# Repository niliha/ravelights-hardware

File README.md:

# ravelights-hardware

This repository contains various PCB designs for driving WS28XX LED strips and other light fixtures.

The READMEs in the subdirectories provide more details.

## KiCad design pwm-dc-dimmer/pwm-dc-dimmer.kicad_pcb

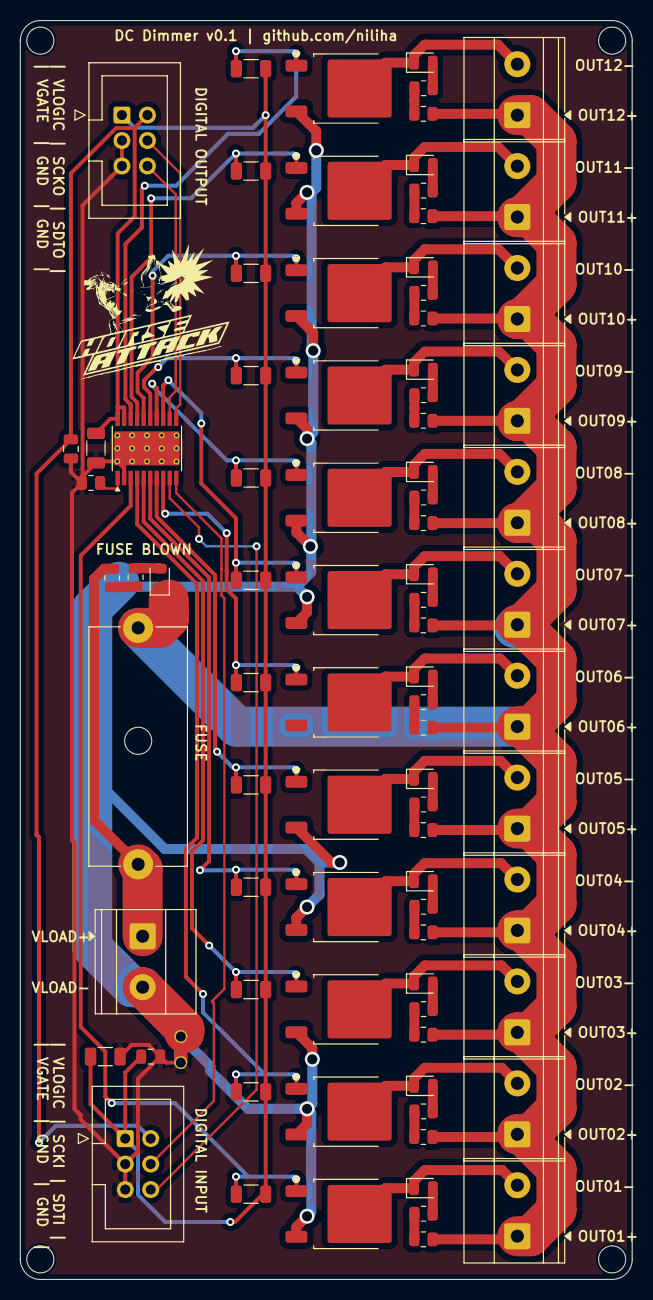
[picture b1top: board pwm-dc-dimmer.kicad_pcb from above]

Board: 2 copper layers, 61.0 x 125.5 mm, 90 parts (0 on the bottom side), 61 nets.

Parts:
C1, C3: 100nF; C_0805_2012Metric
C2, C4: 10uF; C_1206_3216Metric
D1, D2, D3, D4, D5, D6, D7, D8, D9, D10, D11, D12, D13: LED; LED_0805_2012Metric
F1: Fuse; fuseholder
H1, H2, H3, H4: MountingHole; MountingHole_2.7mm_M2.5_ISO7380
J1, J2, J3, J4, J5, J6, J7, J8, J9, J10, J11, J12, J13: Screw_Terminal_01x02; TerminalBlock_Phoenix_MKDS-1,5-2-5.08_1x02_P5.08mm_Horizont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
J14, J15: Conn_02x03_Odd_Even; IDC-Header_2x03_P2.54mm_Vertical
NT1: NetTie_2; NetTie-2_THT_Pad1.0mm
Q1, Q2, Q3, Q4, Q5, Q6, Q7, Q8, Q9, Q10, Q11, Q12: Q_NMOS_GDS; TO-252-2
R1: 3K; R_0805_2012Metric
R2, R3, R4, R5, R6, R7, R8, R9, R10, R11, R12, R13: 300R; R_1206_3216Metric
R14, R15, R16, R17, R18, R19, R20, R21, R22, R23, R24, R25, R26, R27, R28, R29, R30, R31, R32, R33, R34, R35, R36, R37, R38, R39: 10K; R_0805_2012Metric
U1: HTSSOP-20-1EP_4.4x6.5mm_P0.65mm_EP3.4x6.5mm_ThermalVias

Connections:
/Channel 1/LED_LOAD_BETWEEN_RESISTORS: R14.2, R26.1
/Channel 1/LED_LOAD_CATHODE: D1.2 (A), R26.2
/Channel 2/LED_LOAD_BETWEEN_RESISTORS: R15.2, R27.1
/Channel 2/LED_LOAD_CATHODE: D2.2 (A), R27.2
/Channel 3/LED_LOAD_BETWEEN_RESISTORS: R16.2, R28.1
/Channel 3/LED_LOAD_CATHODE: D3.2 (A), R28.2
/Channel 4/LED_LOAD_BETWEEN_RESISTORS: R17.2, R29.1
/Channel 4/LED_LOAD_CATHODE: D4.2 (A), R29.2
/Channel 5/LED_LOAD_BETWEEN_RESISTORS: R18.2, R30.1
/Channel 5/LED_LOAD_CATHODE: D5.2 (A), R30.2
/Channel 6/LED_LOAD_BETWEEN_RESISTORS: R19.2, R31.1
/Channel 6/LED_LOAD_CATHODE: D6.2 (A), R31.2
/Channel 7/LED_LOAD_BETWEEN_RESISTORS: R20.2, R32.1
/Channel 7/LED_LOAD_CATHODE: D7.2 (A), R32.2
/Channel 8/LED_LOAD_BETWEEN_RESISTORS: R21.2, R33.1
/Channel 8/LED_LOAD_CATHODE: D8.2 (A), R33.2
/Channel 9/LED_LOAD_BETWEEN_RESISTORS: R22.2, R34.1
/Channel 9/LED_LOAD_CATHODE: D9.2 (A), R34.2
/Channel 10/LED_LOAD_BETWEEN_RESISTORS: R23.2, R35.1
/Channel 10/LED_LOAD_CATHODE: D10.2 (A), R35.2
/Channel 11/LED_LOAD_BETWEEN_RESISTORS: R24.2, R36.1
/Channel 11/LED_LOAD_CATHODE: D11.2 (A), R36.2
/Channel 12/LED_LOAD_BETWEEN_RESISTORS: R25.2, R37.1
/Channel 12/LED_LOAD_CATHODE: D12.2 (A), R37.2
/FUSE_LED_CATHODE: D13.2 (A), R39.2
/FUSE_LED_RESISTORS: R38.2, R39.1
GATE_SINK_1: Q1.1 (G), R3.2, U1.3 (OUT0)
GATE_SINK_2: Q2.1 (G), R2.2, U1.4 (OUT1)
GATE_SINK_3: Q3.1 (G), R4.2, U1.5 (OUT2)
GATE_SINK_4: Q4.1 (G), R5.2, U1.6 (OUT3)
GATE_SINK_5: Q5.1 (G), R6.2, U1.7 (OUT4)
GATE_SINK_6: Q6.1 (G), R7.2, U1.8 (OUT5)
GATE_SINK_7: Q7.1 (G), R8.2, U1.13 (OUT6)
GATE_SINK_8: Q8.1 (G), R9.2, U1.14 (OUT7)
GATE_SINK_9: Q9.1 (G), R10.2, U1.15 (OUT8)
GATE_SINK_10: Q10.1 (G), R11.2, U1.16 (OUT9)
GATE_SINK_11: Q11.1 (G), R12.2, U1.17 (OUT10)
GATE_SINK_12: Q12.1 (G), R13.2, U1.18 (OUT11)
GND: C1.2, C2.2, C3.2, C4.2, J14.3, J14.5, J15.3, J15.5, NT1.2, R1.2, U1.2 (GND), U1.21 (EP)
GND_LOAD: J13.2, NT1.1, Q1.3 (S), Q2.3 (S), Q3.3 (S), Q4.3 (S), Q5.3 (S), Q6.3 (S), Q7.3 (S), Q8.3 (S), Q9.3 (S), Q10.3 (S), Q11.3 (S), Q12.3 (S)
unnamed: R1.1, U1.1 (IREF)
OUT1-: D1.1 (K), J1.2, Q1.2 (D)
OUT2-: D2.1 (K), J2.2, Q2.2 (D)
OUT3-: D3.1 (K), J3.2, Q3.2 (D)
OUT4-: D4.1 (K), J4.2, Q4.2 (D)
OUT5-: D5.1 (K), J5.2, Q5.2 (D)
OUT6-: D6.1 (K), J6.2, Q6.2 (D)
OUT7-: D7.1 (K), J7.2, Q7.2 (D)
OUT8-: D8.1 (K), J8.2, Q8.2 (D)
OUT9-: D9.1 (K), J9.2, Q9.2 (D)
OUT10-: D10.1 (K), J10.2, Q10.2 (D)
OUT11-: D11.1 (K), J11.2, Q11.2 (D)
OUT12-: D12.1 (K), J12.2, Q12.2 (D)
SCKI: J15.4, U1.10 (SCKI)
SCKO: J14.4, U1.11 (SCKO)
SDTI: J15.6, U1.9 (SDTI)
SDTO: J14.6, U1.12 (SDTO)
V_GATE: C3.1, C4.1, J14.1, J15.1, R2.1, R3.1, R4.1, R5.1, R6.1, R7.1, R8.1, R9.1, R10.1, R11.1, R12.1, R13.1
V_LOAD: F1.1, J13.1, R38.1
V_LOAD_FUSED: D13.1 (K), F1.2, J1.1, J2.1, J3.1, J4.1, J5.1, J6.1, J7.1, J8.1, J9.1, J10.1, J11.1, J12.1, R14.1, R15.1, R16.1, R17.1, R18.1, R19.1, R20.1, R21.1, R22.1, R23.1, R24.1, R25.1
V_LOGIC: C1.1, C2.1, J14.2, J15.2, U1.19 (VCC), U1.20 (VREG)

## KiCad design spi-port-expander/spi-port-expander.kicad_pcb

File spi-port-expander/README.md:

# SPI Port Expander

This is a breakout board for the [MCP23S17](https://www.microchip.com/en-us/product/MCP23S17) 16 channel SPI port expander.
Using hardware addressing mode, 8 of these port expanders can be driven on a single SPI bus with the same chip select line.

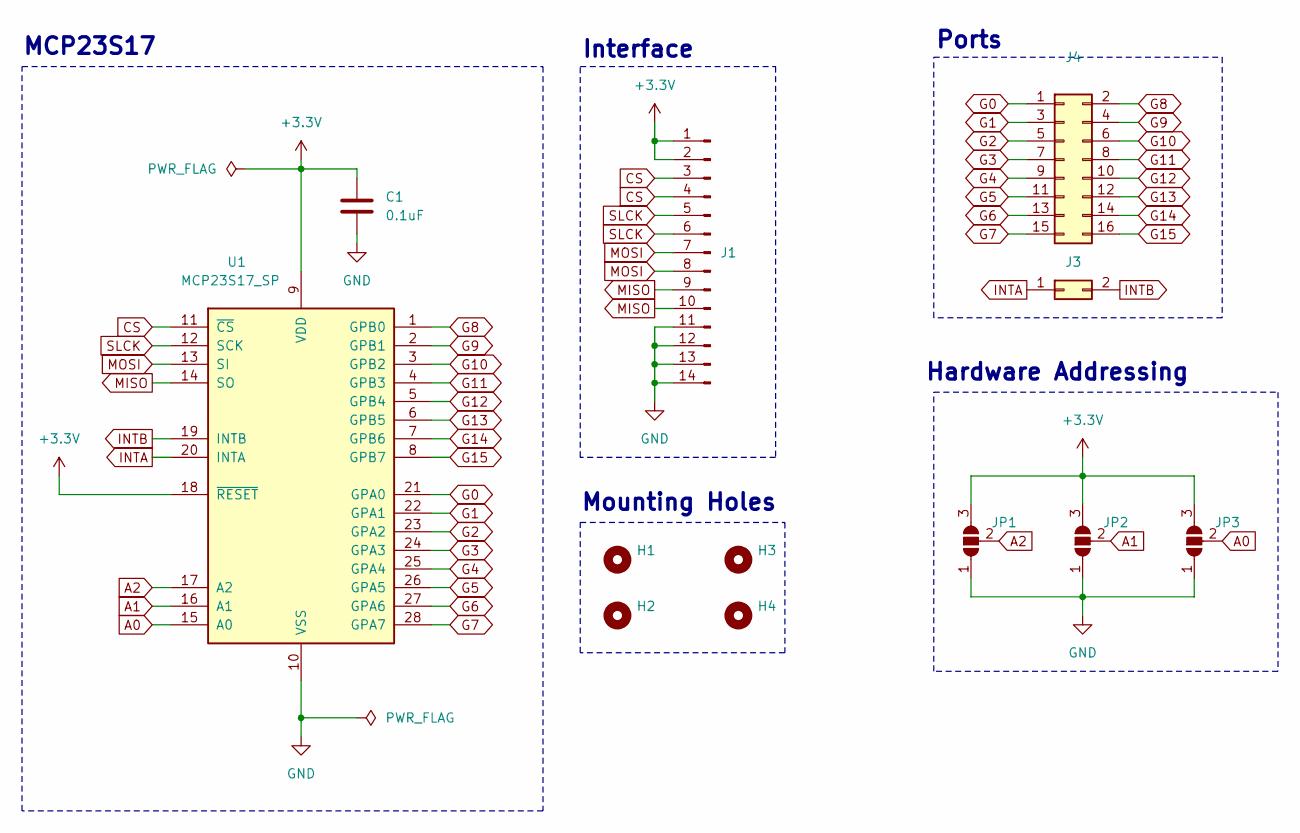
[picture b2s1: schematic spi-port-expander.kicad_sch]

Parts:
C1: 0.1uF; C_Disc_D5.0mm_W2.5mm_P5.00mm
H1, H2, H3, H4: MountingHole; MountingHole_2.7mm_M2.5
J1: Conn_01x14_Pin; PinHeader_1x14_P2.54mm_Vertical
J3: Conn_02x01; PinHeader_2x01_P2.54mm_Vertical
J4: Conn_02x08_Odd_Even; PinHeader_2x08_P2.54mm_Vertical
JP1, JP2, JP3: SolderJumper_3_Open; SolderJumper-3_P1.3mm_Open_Pad1.0x1.5mm
U1: MCP23S17_SP; DIP-28_W7.62mm

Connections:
+3.3V: C1.1, J1.1, J1.2, JP1.3 (B), JP2.3 (B), JP3.3 (B), U1.9 (VDD), U1.18 (~RESET)
A0: JP3.2 (C), U1.15 (A0)
A1: JP2.2 (C), U1.16 (A1)
A2: JP1.2 (C), U1.17 (A2)
CS: J1.3, J1.4, U1.11 (~CS)
G0: J4.1, U1.21 (GPA0)
G1: J4.3, U1.22 (GPA1)
G2: J4.5, U1.23 (GPA2)
G3: J4.7, U1.24 (GPA3)
G4: J4.9, U1.25 (GPA4)
G5: J4.11, U1.26 (GPA5)
G6: J4.13, U1.27 (GPA6)
G7: J4.15, U1.28 (GPA7)
G8: J4.2, U1.1 (GPB0)
G9: J4.4, U1.2 (GPB1)
G10: J4.6, U1.3 (GPB2)
G11: J4.8, U1.4 (GPB3)
G12: J4.10, U1.5 (GPB4)
G13: J4.12, U1.6 (GPB5)
G14: J4.14, U1.7 (GPB6)
G15: J4.16, U1.8 (GPB7)
GND: C1.2, J1.11, J1.12, J1.13, J1.14, JP1.1 (A), JP2.1 (A), JP3.1 (A), U1.10 (VSS)
INTA: J3.1, U1.20 (INTA)
INTB: J3.2, U1.19 (INTB)
MISO: J1.9, J1.10, U1.14 (SO)
MOSI: J1.7, J1.8, U1.13 (SI)
SLCK: J1.5, J1.6, U1.12 (SCK)

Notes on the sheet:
Ports
MCP23S17
Interface
Hardware Addressing
Mounting Holes

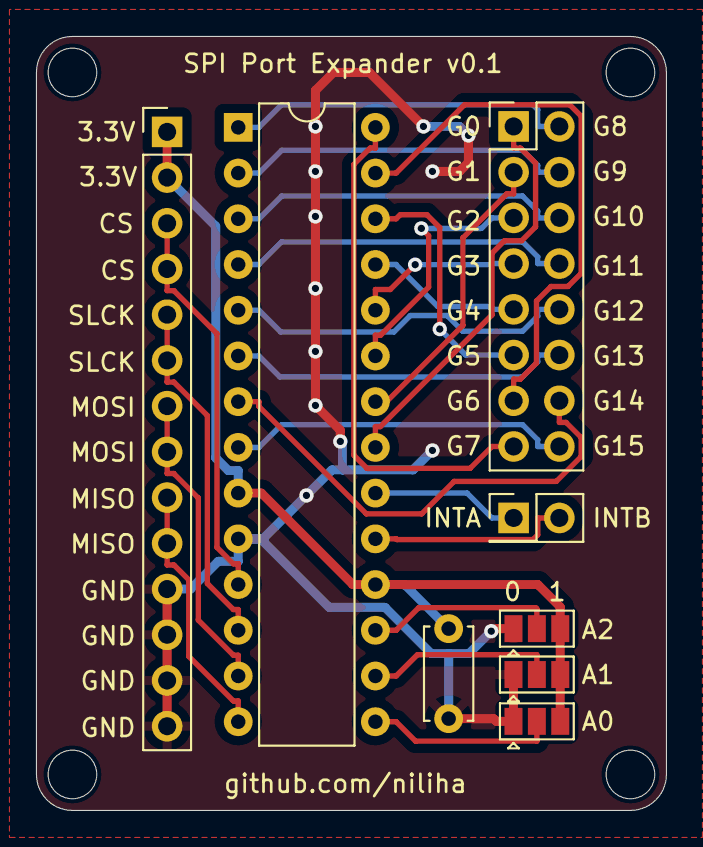
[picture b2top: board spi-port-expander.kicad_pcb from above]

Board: 2 copper layers, 35.0 x 43.0 mm, 12 parts (0 on the bottom side), 27 nets.

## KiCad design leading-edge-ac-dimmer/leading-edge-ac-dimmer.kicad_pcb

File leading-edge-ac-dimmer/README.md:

# Leading Edge 230V AC Dimmer

This PCB design allows to dim 8 incandescent light bulbs using a microcontroller.

**Note:** In version v0.1 there is a design error which leads to arcing on the snubber resistor.
This can be fixed by omitting the snubber circuit at the cost of not being able to drive inductive loads.
In a future revision, the snubber resistor will be replaced with a more suitable one.

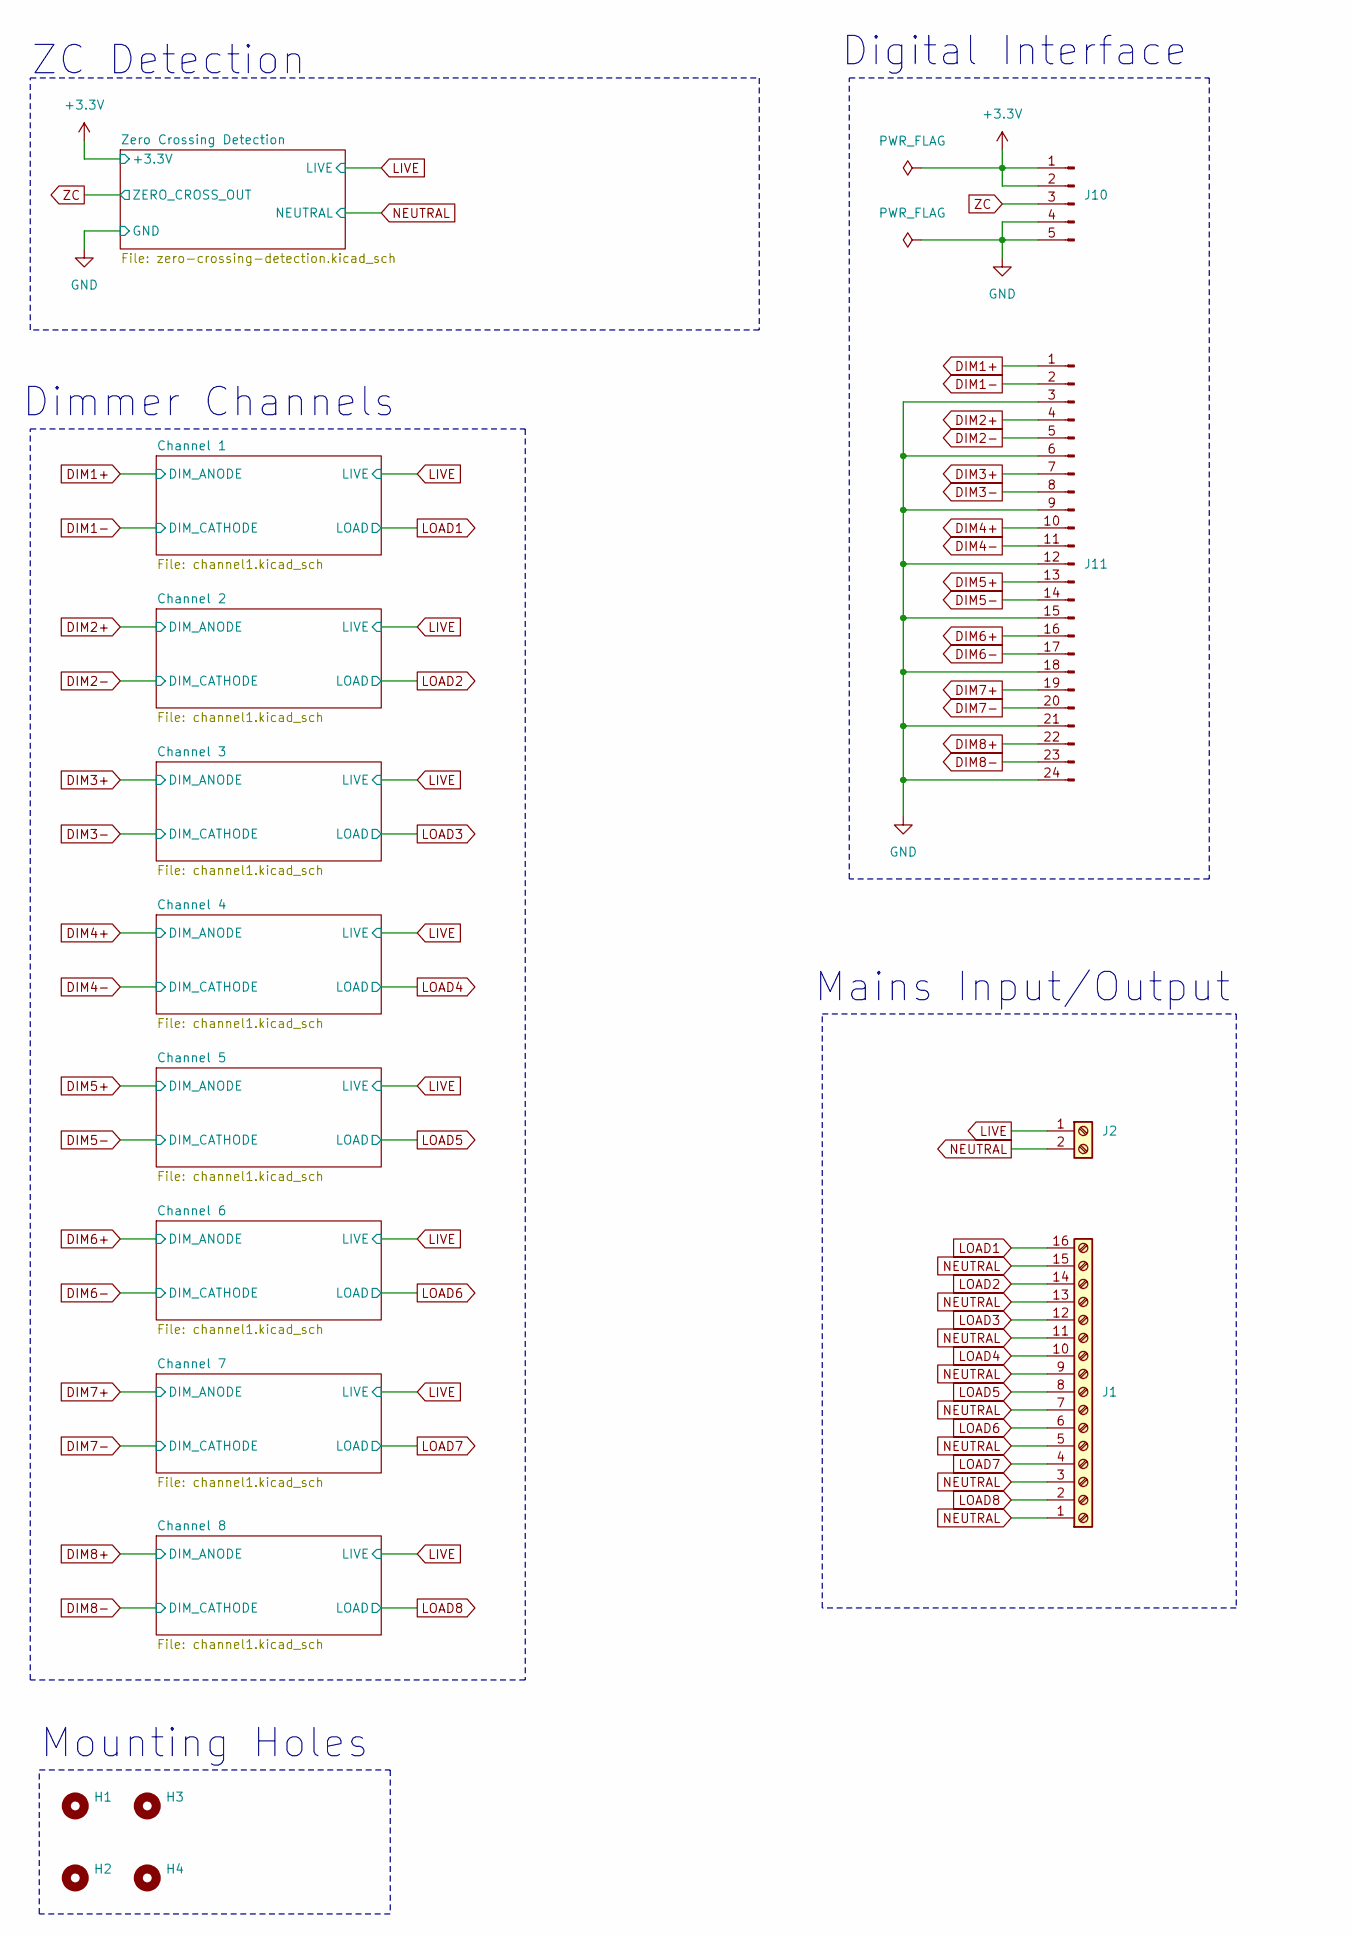
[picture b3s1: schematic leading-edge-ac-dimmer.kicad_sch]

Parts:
H1, H2, H3, H4: MountingHole; MountingHole_2.7mm_M2.5_ISO7380
J1: Screw_Terminal_01x16; TerminalBlock_Phoenix_MKDS-1,5-16-5.08_1x16_P5.08mm_Horizon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
J2: Screw_Terminal_01x02; TerminalBlock_Phoenix_MKDS-1,5-2-5.08_1x02_P5.08mm_Horizont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
J10: Conn_01x05_Pin; PinHeader_1x05_P2.54mm_Vertical
J11: Conn_01x24_Pin; PinHeader_1x24_P2.54mm_Vertical

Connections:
+3.3V: J10.1, J10.2; also elsewhere on the board
DIM1+: J11.1; also elsewhere on the board
DIM1-: J11.2; also elsewhere on the board
DIM2+: J11.4; also elsewhere on the board
DIM2-: J11.5; also elsewhere on the board
DIM3+: J11.7; also elsewhere on the board
DIM3-: J11.8; also elsewhere on the board
DIM4+: J11.10; also elsewhere on the board
DIM4-: J11.11; also elsewhere on the board
DIM5+: J11.13; also elsewhere on the board
DIM5-: J11.14; also elsewhere on the board
DIM6+: J11.16; also elsewhere on the board
DIM6-: J11.17; also elsewhere on the board
DIM7+: J11.19; also elsewhere on the board
DIM7-: J11.20; also elsewhere on the board
DIM8+: J11.22; also elsewhere on the board
DIM8-: J11.23; also elsewhere on the board
GND: J10.4, J10.5, J11.3, J11.6, J11.9, J11.12, J11.15, J11.18, J11.21, J11.24; also elsewhere on the board
LIVE: J2.1; also elsewhere on the board
LOAD1: J1.16; also elsewhere on the board
LOAD2: J1.14; also elsewhere on the board
LOAD3: J1.12; also elsewhere on the board
LOAD4: J1.10; also elsewhere on the board
LOAD5: J1.8; also elsewhere on the board
LOAD6: J1.6; also elsewhere on the board
LOAD7: J1.4; also elsewhere on the board
LOAD8: J1.2; also elsewhere on the board
NEUTRAL: J1.1, J1.3, J1.5, J1.7, J1.9, J1.11, J1.13, J1.15, J2.2; also elsewhere on the board
ZC: J10.3; also elsewhere on the board

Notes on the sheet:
Digital Interface
Mounting Holes
Dimmer Channels
Mains Input/Output
ZC Detection

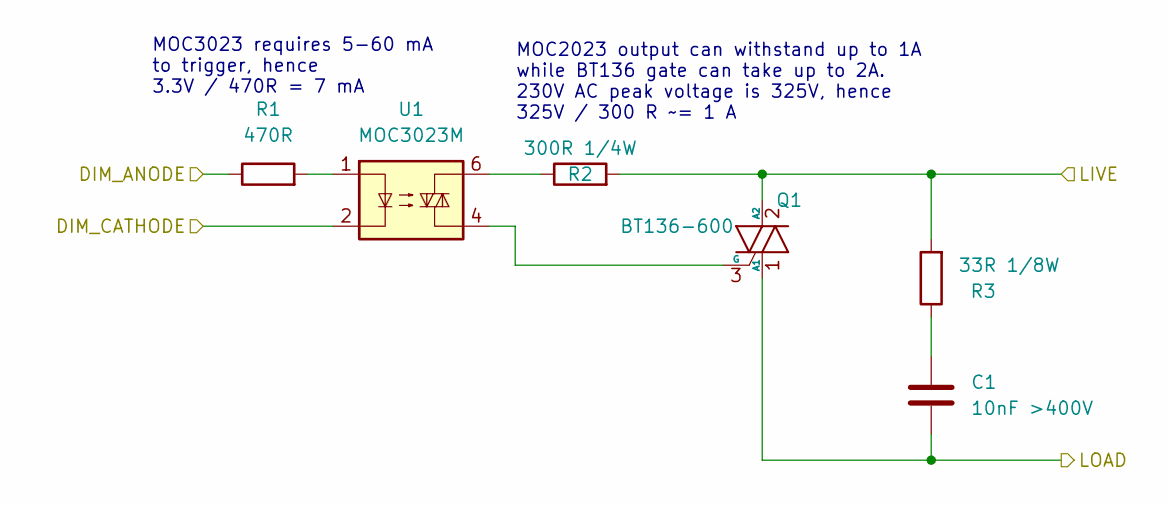
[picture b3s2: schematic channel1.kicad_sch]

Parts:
C1: 10nF >400V; C_1206_3216Metric
Q1: BT136-600; TO-252-2
R1: 470R; R_0805_2012Metric
R2: 300R 1/4W; R_1206_3216Metric
R3: 33R 1/8W; R_0805_2012Metric
U1: MOC3023M; Lite-On_SOP6_6.5x7.3mm_P2.54mm

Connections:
DIM1+: R1.1; also elsewhere on the board
DIM1-: U1.2; also elsewhere on the board
LIVE: Q1.2 (A2), R2.2, R3.2; also elsewhere on the board
LOAD1: C1.2, Q1.1 (A1); also elsewhere on the board
unnamed: C1.1, R3.1
unnamed: Q1.3 (G), U1.4
unnamed: R1.2, U1.1
unnamed: R2.1, U1.6

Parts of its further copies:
C2, C3, C4, C5, C6, C7, C8: 10nF >400V; C_1206_3216Metric
Q2, Q3, Q4, Q5, Q6, Q7, Q8: BT136-600; TO-252-2
R4, R7, R10, R13, R16, R19, R22: 470R; R_0805_2012Metric
R5, R8, R11, R14, R17, R20, R23: 300R 1/4W; R_1206_3216Metric
R6, R9, R12, R15, R18, R21, R24: 33R 1/8W; R_0805_2012Metric
U2, U3, U4, U5, U6, U7, U8: MOC3023M; Lite-On_SOP6_6.5x7.3mm_P2.54mm

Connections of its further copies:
DIM2+: R4.1; also elsewhere on the board
DIM2-: U2.2; also elsewhere on the board
DIM3+: R7.1; also elsewhere on the board
DIM3-: U3.2; also elsewhere on the board
DIM4+: R10.1; also elsewhere on the board
DIM4-: U4.2; also elsewhere on the board
DIM5+: R13.1; also elsewhere on the board
DIM5-: U5.2; also elsewhere on the board
DIM6+: R16.1; also elsewhere on the board
DIM6-: U6.2; also elsewhere on the board
DIM7+: R19.1; also elsewhere on the board
DIM7-: U7.2; also elsewhere on the board
DIM8+: R22.1; also elsewhere on the board
DIM8-: U8.2; also elsewhere on the board
LIVE: Q2.2 (A2), Q3.2 (A2), Q4.2 (A2), Q5.2 (A2), Q6.2 (A2), Q7.2 (A2), Q8.2 (A2), R5.2, R6.2, R8.2, R9.2, R11.2, R12.2, R14.2, R15.2, R17.2, R18.2, R20.2, R21.2, R23.2, R24.2; also elsewhere on the board
LOAD2: C2.2, Q2.1 (A1); also elsewhere on the board
LOAD3: C3.2, Q3.1 (A1); also elsewhere on the board
LOAD4: C4.2, Q4.1 (A1); also elsewhere on the board
LOAD5: C5.2, Q5.1 (A1); also elsewhere on the board
LOAD6: C6.2, Q6.1 (A1); also elsewhere on the board
LOAD7: C7.2, Q7.1 (A1); also elsewhere on the board
LOAD8: C8.2, Q8.1 (A1); also elsewhere on the board
unnamed: C2.1, R6.1
unnamed: C3.1, R9.1
unnamed: C4.1, R12.1
unnamed: C5.1, R15.1
unnamed: C6.1, R18.1
unnamed: C7.1, R21.1
unnamed: C8.1, R24.1
unnamed: Q2.3 (G), U2.4
unnamed: Q3.3 (G), U3.4
unnamed: Q4.3 (G), U4.4
unnamed: Q5.3 (G), U5.4
unnamed: Q6.3 (G), U6.4
unnamed: Q7.3 (G), U7.4
unnamed: Q8.3 (G), U8.4
unnamed: R4.2, U2.1
unnamed: R5.1, U2.6
unnamed: R7.2, U3.1
unnamed: R8.1, U3.6
unnamed: R10.2, U4.1
unnamed: R11.1, U4.6
unnamed: R13.2, U5.1
unnamed: R14.1, U5.6
unnamed: R16.2, U6.1
unnamed: R17.1, U6.6
unnamed: R19.2, U7.1
unnamed: R20.1, U7.6
unnamed: R22.2, U8.1
unnamed: R23.1, U8.6

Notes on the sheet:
MOC2023 output can withstand up to 1A while BT136 gate can take up to 2A. 230V AC peak voltage is 325V, hence 325V / 300 R ~= 1 A
MOC3023 requires 5-60 mA to trigger, hence 3.3V / 470R = 7 mA

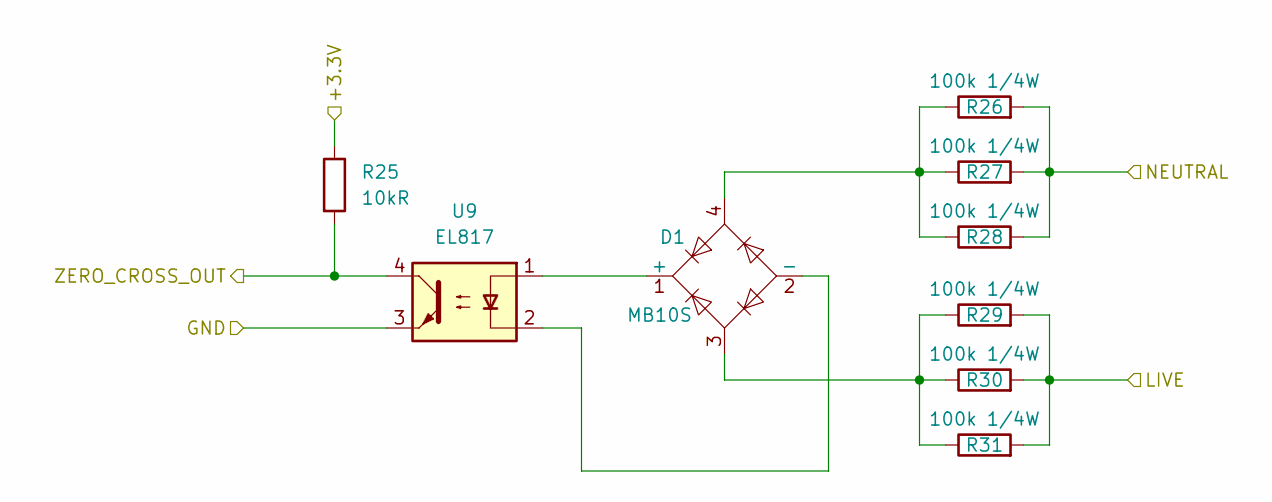
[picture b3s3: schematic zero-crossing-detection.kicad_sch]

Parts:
D1: MB10S; TO-269AA
R25: 10kR; R_0805_2012Metric
R26, R27, R28, R29, R30, R31: 100k 1/4W; R_1206_3216Metric
U9: EL817; SMDIP-4_W9.53mm

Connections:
+3.3V: R25.1; also elsewhere on the board
GND: U9.3; also elsewhere on the board
LIVE: R29.2, R30.2, R31.2; also elsewhere on the board
NEUTRAL: R26.2, R27.2, R28.2; also elsewhere on the board
unnamed: D1.1 (+), U9.1
unnamed: D1.2 (-), U9.2
unnamed: D1.3, R29.1, R30.1, R31.1
unnamed: D1.4, R26.1, R27.1, R28.1
ZC: R25.2, U9.4; also elsewhere on the board

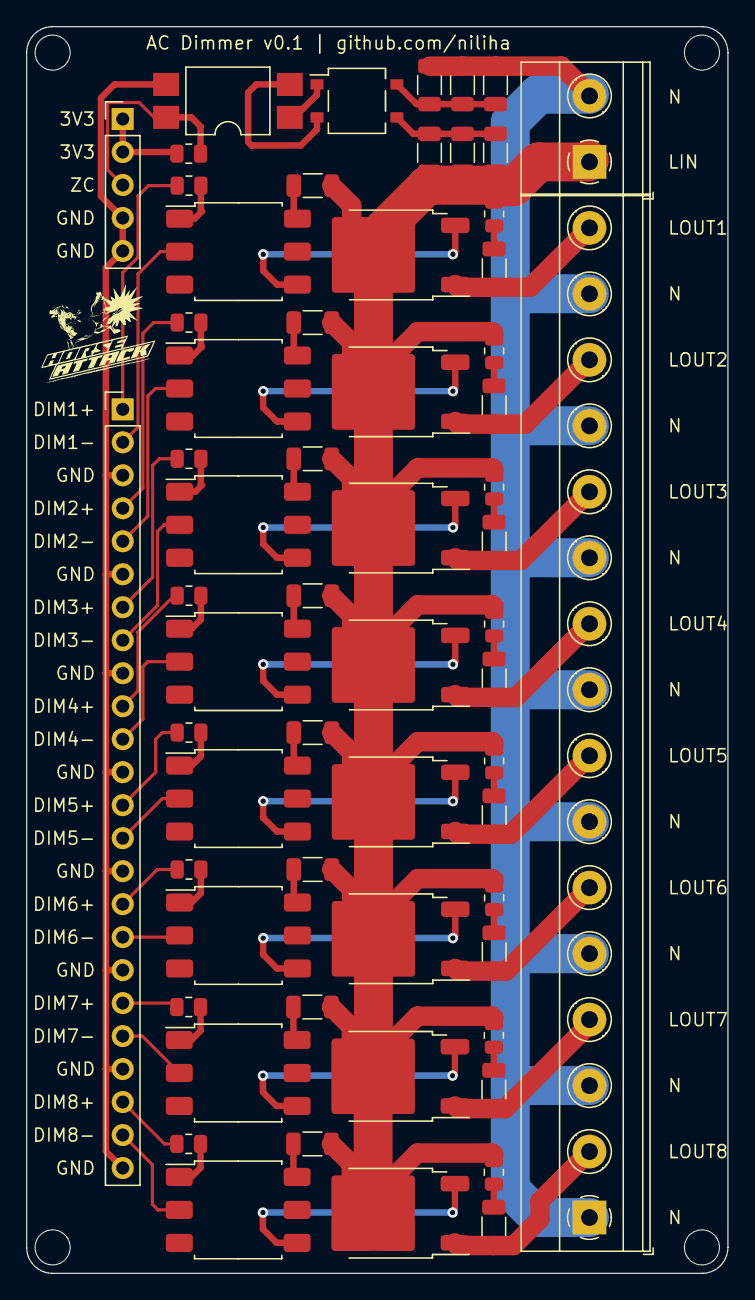
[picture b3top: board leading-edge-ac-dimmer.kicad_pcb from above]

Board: 2 copper layers, 54.0 x 96.0 mm, 65 parts (0 on the bottom side), 65 nets.

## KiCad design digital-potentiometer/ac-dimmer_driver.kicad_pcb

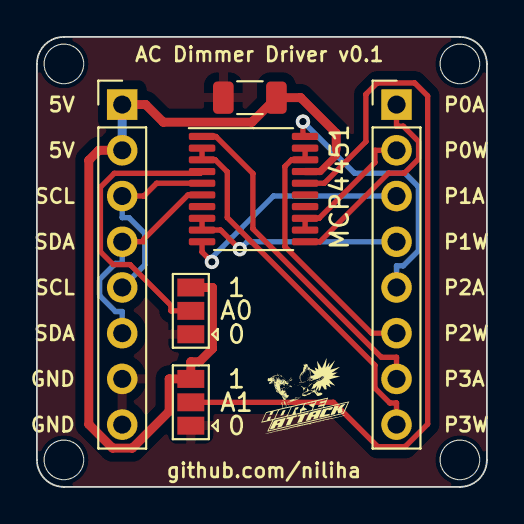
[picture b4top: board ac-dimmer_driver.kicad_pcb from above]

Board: 2 copper layers, 25.0 x 25.0 mm, 10 parts (0 on the bottom side), 14 nets.

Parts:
C1: 0.1uF; C_1206_3216Metric
H1, H2, H3, H4: MountingHole; MountingHole_2.2mm_M2
J1, J2: Conn_01x08_Pin; PinHeader_1x08_P2.54mm_Vertical
JP1, JP2: SolderJumper_3_Open; SolderJumper-3_P1.3mm_Open_Pad1.0x1.5mm
U1: MCP4451; TSSOP-20_4.4x6.5mm_P0.65mm

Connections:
+5V: C1.1, J2.1, J2.2, JP1.3 (B), JP2.3 (B), U1.17 (VDD)
/A0: JP1.2 (C), U1.4 (HVC/A0)
/A1: JP2.2 (C), U1.16 (A1)
GND: C1.2, J2.7, J2.8, JP1.1 (A), JP2.1 (A), U1.7 (VSS)
P0A: J1.1, U1.11 (P0A)
P0W: J1.2, U1.12 (P0W), U1.13 (P0B)
P1A: J1.3, U1.10 (P1A)
P1W: J1.4, U1.8 (P1B), U1.9 (P1W)
P2A: J1.5, U1.20 (P2A)
P2W: J1.6, U1.18 (P2B), U1.19 (P2W)
P3A: J1.7, U1.1 (P3A)
P3W: J1.8, U1.2 (P3W), U1.3 (P3B)
SCL_MCU: J2.3, J2.5, U1.5 (SCL)
SDA_MCU: J2.4, J2.6, U1.6 (SDA)

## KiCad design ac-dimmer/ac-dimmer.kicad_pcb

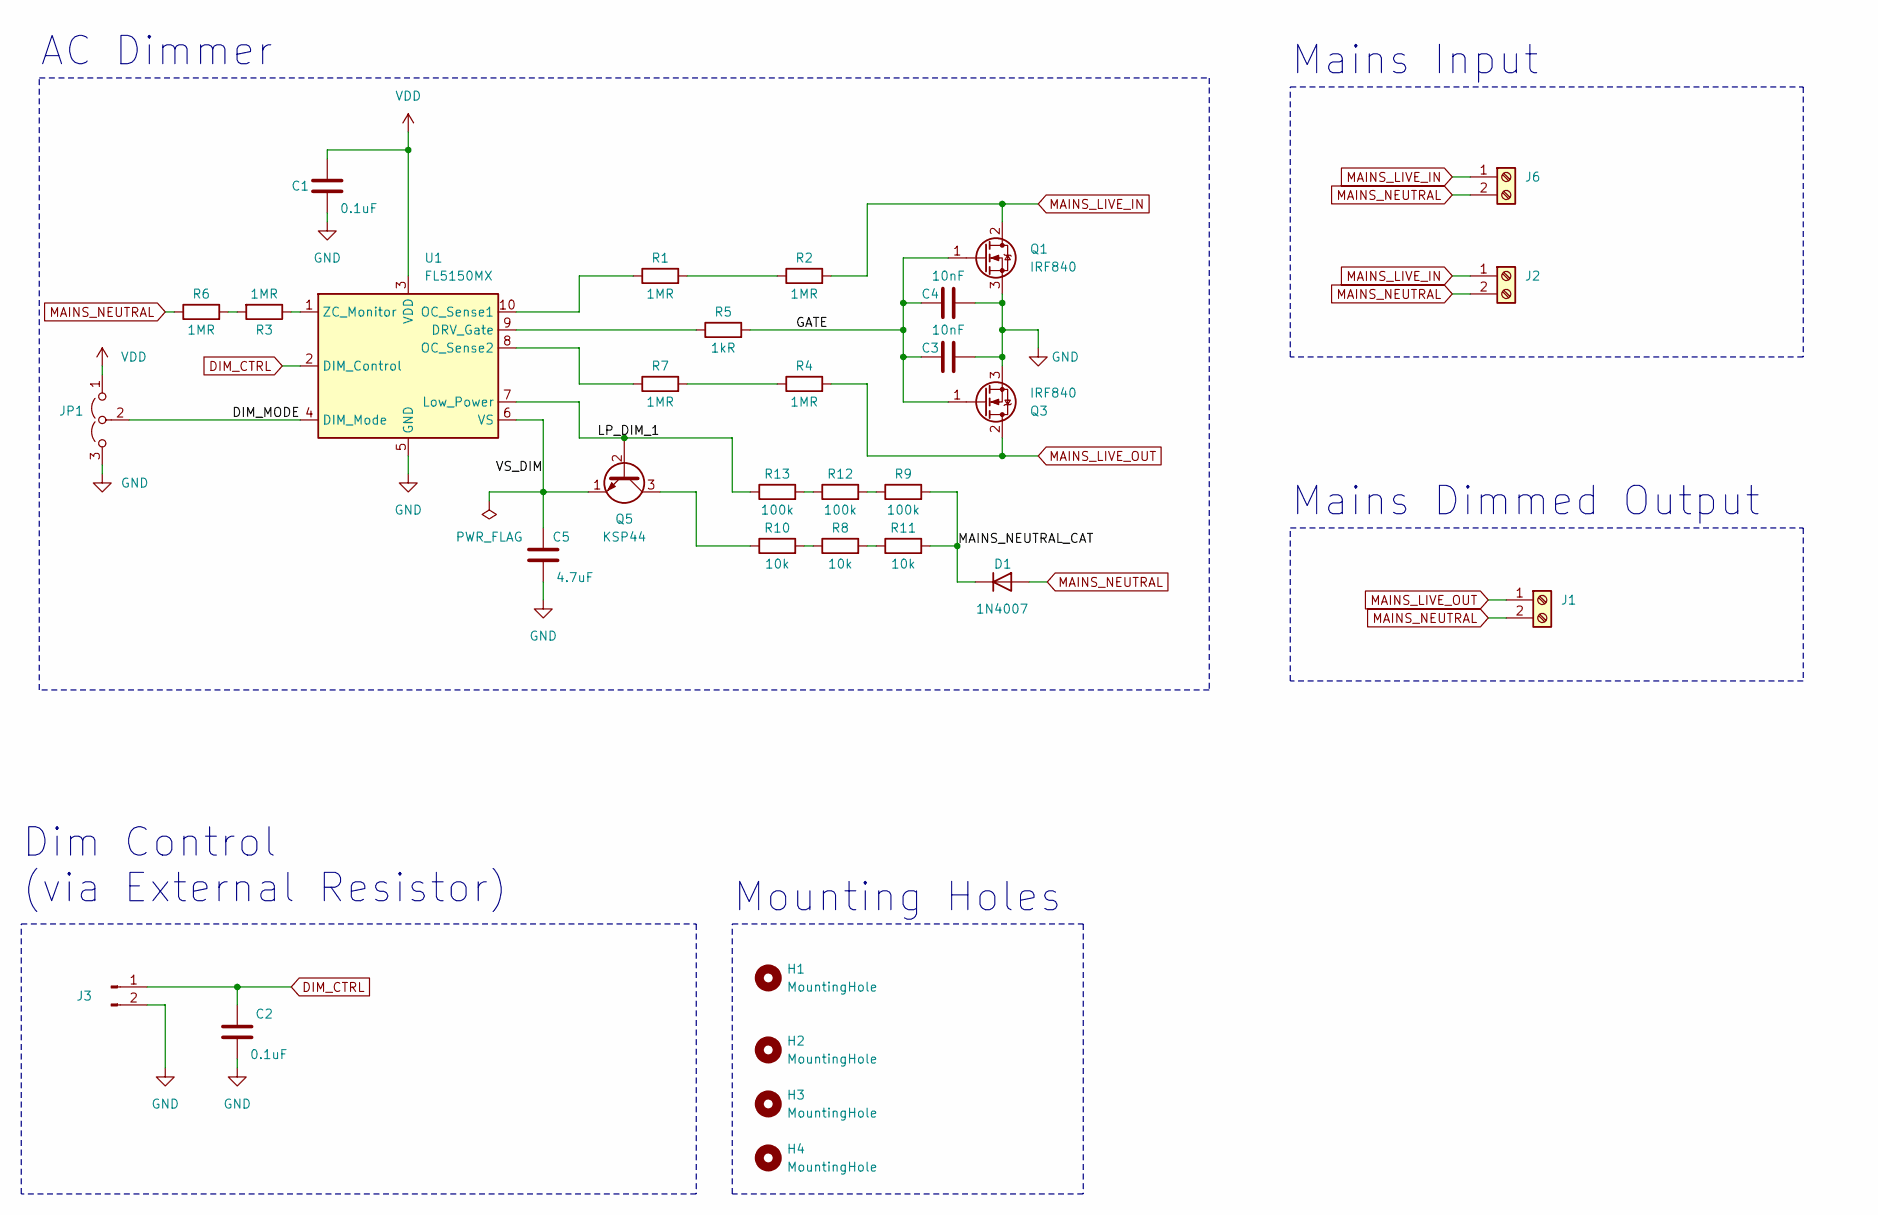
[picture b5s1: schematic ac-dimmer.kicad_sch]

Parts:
C1, C2: 0.1uF; C_1206_3216Metric
C3, C4: 10nF; C_1206_3216Metric
C5: 4.7uF; C_1206_3216Metric
D1: 1N4007; D_DO-41_SOD81_P10.16mm_Horizontal
H1, H2, H3, H4: MountingHole; MountingHole_2.7mm_M2.5_ISO7380
J1, J2, J6: Screw_Terminal_01x02; TerminalBlock_Phoenix_MKDS-1,5-2-5.08_1x02_P5.08mm_Horizont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
J3: Conn_01x02_Pin; PinHeader_1x02_P2.54mm_Vertical
JP1: Jumper_3_Open; PinHeader_1x03_P2.54mm_Vertical
Q1, Q3: IRF840; TO-220-3_Vertical
Q5: KSP44; TO-92_Inline
R1, R2, R3, R4, R6, R7: 1MR; R_1206_3216Metric
R5: 1kR; R_1206_3216Metric
R8, R10, R11: 10k; R_1206_3216Metric
R9, R12, R13: 100k; R_1206_3216Metric
U1: FL5150MX; SSOP-10_3.9x4.9mm_P1.00mm

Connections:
/DIM_MODE: JP1.2 (C), U1.4 (DIM_Mode)
/GATE: C3.1, C4.1, Q1.1 (G), Q3.1 (G), R5.2
/LP_DIM_1: Q5.2 (B), R13.1, U1.7 (Low_Power)
/MAINS_NEUTRAL_CAT: D1.1 (K), R9.2, R11.2
/VS_DIM: C5.1, Q5.1 (E), U1.6 (VS)
DIM_CTRL: C2.1, J3.1, U1.2 (DIM_Control)
GND: C1.2, C2.2, C3.2, C4.2, C5.2, J3.2, JP1.3 (B), Q1.3 (S), Q3.3 (S), U1.5 (GND)
MAINS_LIVE_IN: J2.1, J6.1, Q1.2 (D), R2.2
MAINS_LIVE_OUT: J1.1, Q3.2 (D), R4.2
MAINS_NEUTRAL: D1.2 (A), J1.2, J2.2, J6.2, R6.1
unnamed: Q5.3 (C), R10.1
unnamed: R1.2, R2.1
unnamed: R3.2, R6.2
unnamed: R4.1, R7.2
unnamed: R8.1, R10.2
unnamed: R8.2, R11.1
unnamed: R12.1, R13.2
unnamed: R9.1, R12.2
unnamed: R5.1, U1.9 (DRV_Gate)
unnamed: R1.1, U1.10 (OC_Sense1)
unnamed: R7.1, U1.8 (OC_Sense2)
unnamed: R3.1, U1.1 (ZC_Monitor)
VDD: C1.1, JP1.1 (A), U1.3 (VDD)

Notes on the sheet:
Mains Input
AC Dimmer
Mounting Holes
Dim Control (via External Resistor)
Mains Dimmed Output

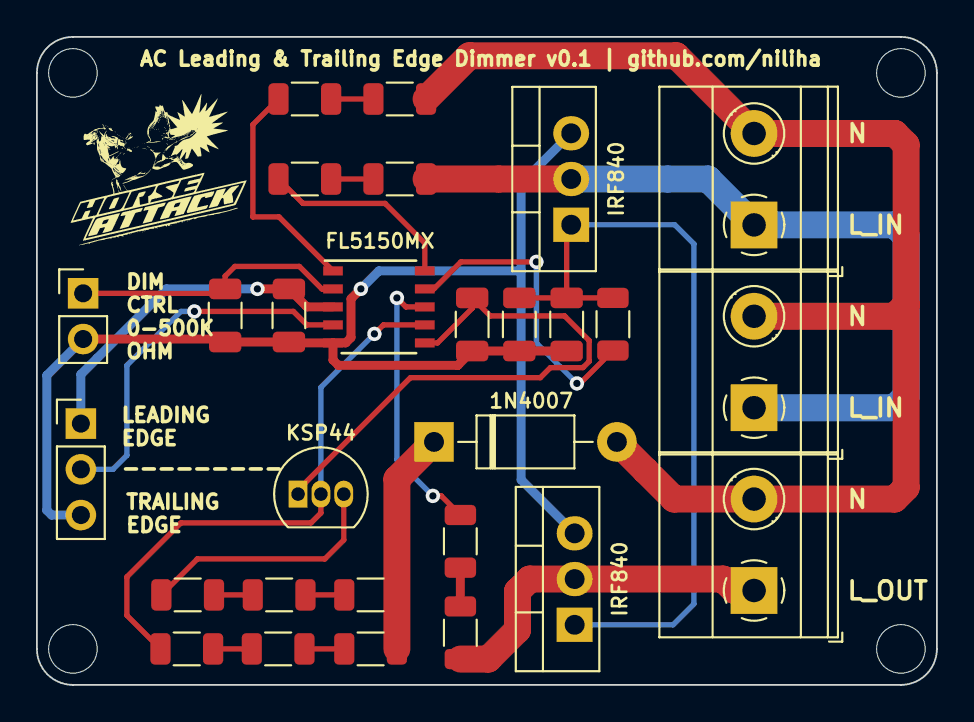
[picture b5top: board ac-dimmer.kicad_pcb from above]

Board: 2 copper layers, 50.0 x 36.0 mm, 32 parts (0 on the bottom side), 23 nets.
